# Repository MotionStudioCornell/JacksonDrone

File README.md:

# JacksonDrone

For the build guide, documentation, and more, please check out our [Wiki page](https://github.com/MotionStudioCornell/JacksonDrone/wiki).

# Getting Started

Clone the project
```
git clone https://github.com/MotionStudioCornell/JacksonDrone.git
```

Go to the software dir.
```
cd JacksonDrone && cd software
```

Build the project

```
./builder
```

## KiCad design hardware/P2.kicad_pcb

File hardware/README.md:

# Schematics
KiCad Schematics

*Note: please export the schematics to `P2.svg` so this README can preview it correctly*

The controller software can be found here: https://github.com/MotionStudioCornell/P2

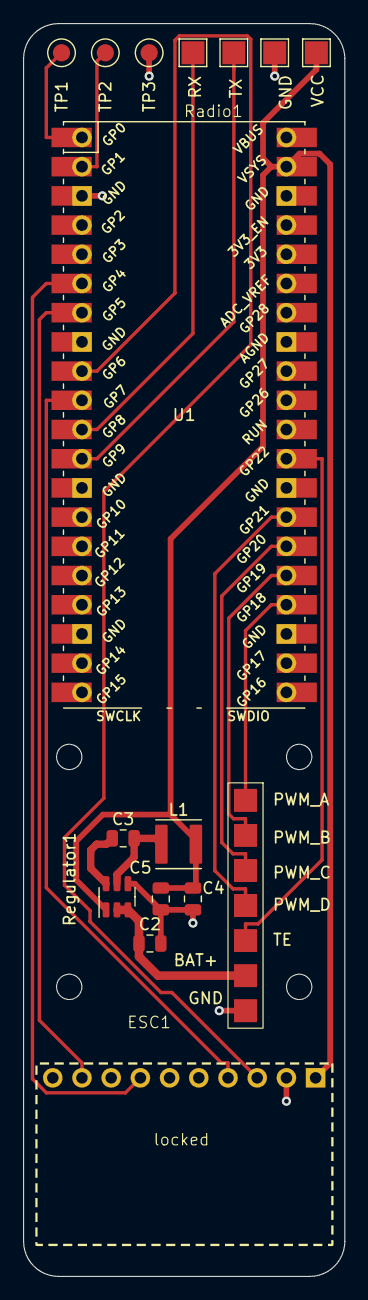
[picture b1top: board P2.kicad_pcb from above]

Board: 2 copper layers, 27.9 x 109.0 mm, 17 parts (0 on the bottom side), 18 nets.

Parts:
C2: 10uF; C_0805_2012Metric
C3: 0.1uF; C_0805_2012Metric
C4, C5: 22uF; C_0805_2012Metric
ESC1: ESC
H1, H2, H3, H4: MountingHole; MountingHole_2.2mm_M2
L1: 4.7uH; L_Abracon_ASPI-4030S
Radio1: Radio
Regulator1: AP63203WU; TSOT-23-6
TP1: TX0; TestPoint_Pad_D2.0mm
TP2: TX1; TestPoint_Pad_D2.0mm
TP3: GND; TestPoint_Pad_D2.0mm
U1: Pico; RPi_Pico_SMD_TH
locked: MPU9250-Breakout

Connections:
+3V3: C4.1, C5.1, L1.2, Radio1.1 (VCC), Regulator1.1 (FB), U1.39 (VSYS), locked.1 (VCC)
+BATT: C2.1, ESC1.5 (BAT+), Regulator1.2 (EN), Regulator1.3 (IN)
/CS: U1.7 (GPIO5), locked.9 (NCS)
/MISO: U1.6 (GPIO4), locked.7 (ADO)
/MOSI: U1.10 (GPIO7), locked.4 (SDA)
/PWM_A: ESC1.1 (PWM_A), U1.24 (GPIO18)
/PWM_B: ESC1.2 (PWM_B), U1.25 (GPIO19)
/PWM_C: ESC1.3 (PWM_C), U1.26 (GPIO20)
/PWM_D: ESC1.4 (PWM_D), U1.27 (GPIO21)
/RX: Radio1.3 (TX), U1.12 (GPIO9)
/SCK: U1.9 (GPIO6), locked.3 (SCL)
/TE: ESC1.6 (TE), U1.29 (GPIO22)
/TX: Radio1.4 (RX), U1.11 (GPIO8)
GND: C2.2, C4.2, C5.2, ESC1.7 (GND), Radio1.2 (GND), Regulator1.4 (GND), TP3.1, U1.3 (GND), locked.2 (GND)
unnamed: C3.1, Regulator1.6 (BST)
unnamed: C3.2, L1.1, Regulator1.5 (SW)
unnamed: TP1.1, U1.1 (GPIO0)
unnamed: TP2.1, U1.2 (GPIO1)

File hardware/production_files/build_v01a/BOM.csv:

Designator,Footprint,Comment
C3,C_0805_2012Metric,0.1uF
C2,C_0805_2012Metric,10uF
L1,L_Abracon_ASPI-4030S,4.7uH
Regulator1,TSOT-23-6,AP63203WU
"C4,C5",C_0805_2012Metric,22uF

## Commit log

2024-01-12 britney
2024-02-24 fix .vscode file
2024-02-25 update sche
2024-02-25 add radio
2024-02-25 pre-pcb design
2024-02-26 pcb done
2024-02-26 change pkg
2024-02-26 update svg
2024-03-06 builder scripter
2024-03-10 Low pass filter
2024-03-10 radio lib(not testesd)
2024-03-12 improve UI
2024-03-19 complementry filter lib
2024-03-19 states timecontrol
2024-03-19 push
2024-03-23 P control
2024-03-23 P for roll and pitch, motor bug
2024-03-23 fix motor issue
2024-03-25 D done
2024-03-25 serial UI for Kp and Kd
2024-03-26 serial throttle change
2024-04-07 radio tested
2024-04-14 Integral control
2024-04-16 init arm throttle
2024-04-24 yaw control
2024-06-12 last update on P2
2024-06-19 shell update
2024-06-20 pcb v1, and production files
